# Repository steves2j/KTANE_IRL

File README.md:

# KTANE_IRL
Keep Talking and Nobody Explosed in real Life

#Aid Memory
python3 -m pip install -r ../CanBusSysFirmware/micropython/tools/mpremote/requirements.txt

python3 ../CanBusSysFirmware/micropython/tools/mpremote/mpremote.py connect /dev/cu.usbmodem1411401 fs cp ktane_who_on_first.py :main.py

python3 ../CanBusSysFirmware/micropython/tools/mpremote/mpremote.py connect /dev/cu.usbmodem1411401
exec(open("main.py").read())

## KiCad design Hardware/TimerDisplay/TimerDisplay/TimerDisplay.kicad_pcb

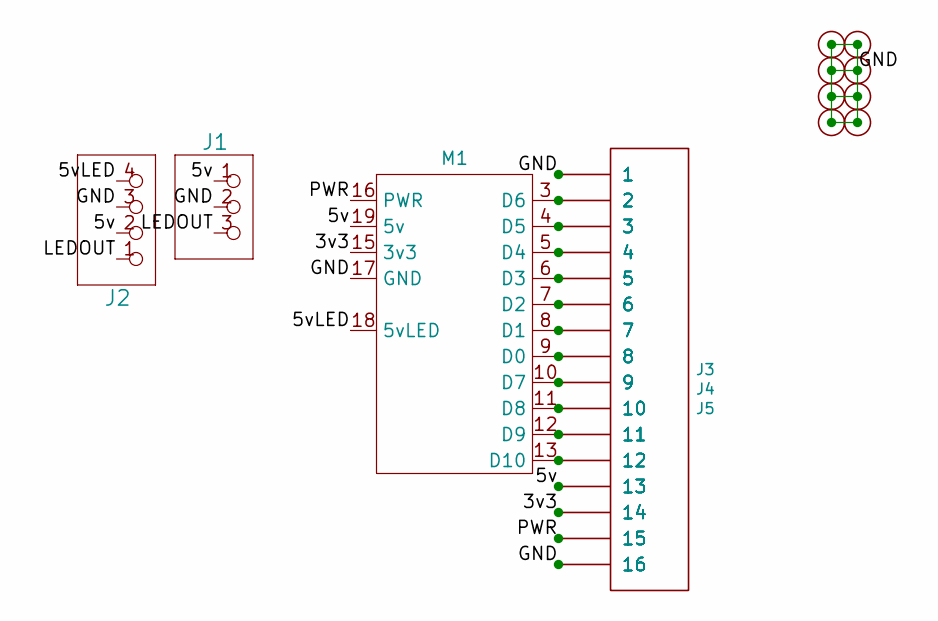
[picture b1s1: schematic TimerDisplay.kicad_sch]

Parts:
H1, H2, H3, H4, H5, H6, H7, H8: Hole; 3mm_pth
J1: HEADER-1X3; 1X03_ROUND
J2: HEADER-1X4; 1X04_LED
J3, J4, J5: HEADER-1X16R; 1X16_ROUND
M1: CanBusModule-BottomCan

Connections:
/3v3: J3.14, J4.14, J5.14, M1.15 (3v3)
/5v: J1.1, J2.2, J3.13, J4.13, J5.13, M1.14 (5v), M1.19 (5v)
/5vLED: J2.4, M1.18 (5vLED)
/GND: H1.1, H2.1, H3.1, H4.1, H5.1, H6.1, H7.1, H8.1, J1.2, J2.3, J3.1, J3.16, J4.1, J4.16, J5.1, J5.16, M1.1 (GND), M1.2 (GND), M1.17 (GND)
/LEDOUT: J1.3, J2.1
/PWR: J3.15, J4.15, J5.15, M1.16 (PWR)
unnamed: J3.8, J4.8, J5.8, M1.9 (D0)
unnamed: J3.7, J4.7, J5.7, M1.8 (D1)
unnamed: J3.6, J4.6, J5.6, M1.7 (D2)
unnamed: J3.5, J4.5, J5.5, M1.6 (D3)
unnamed: J3.4, J4.4, J5.4, M1.5 (D4)
unnamed: J3.3, J4.3, J5.3, M1.4 (D5)
unnamed: J3.2, J4.2, J5.2, M1.3 (D6)
unnamed: J3.9, J4.9, J5.9, M1.10 (D7)
unnamed: J3.10, J4.10, J5.10, M1.11 (D8)
unnamed: J3.11, J4.11, J5.11, M1.12 (D9)
unnamed: J3.12, J4.12, J5.12, M1.13 (D10)

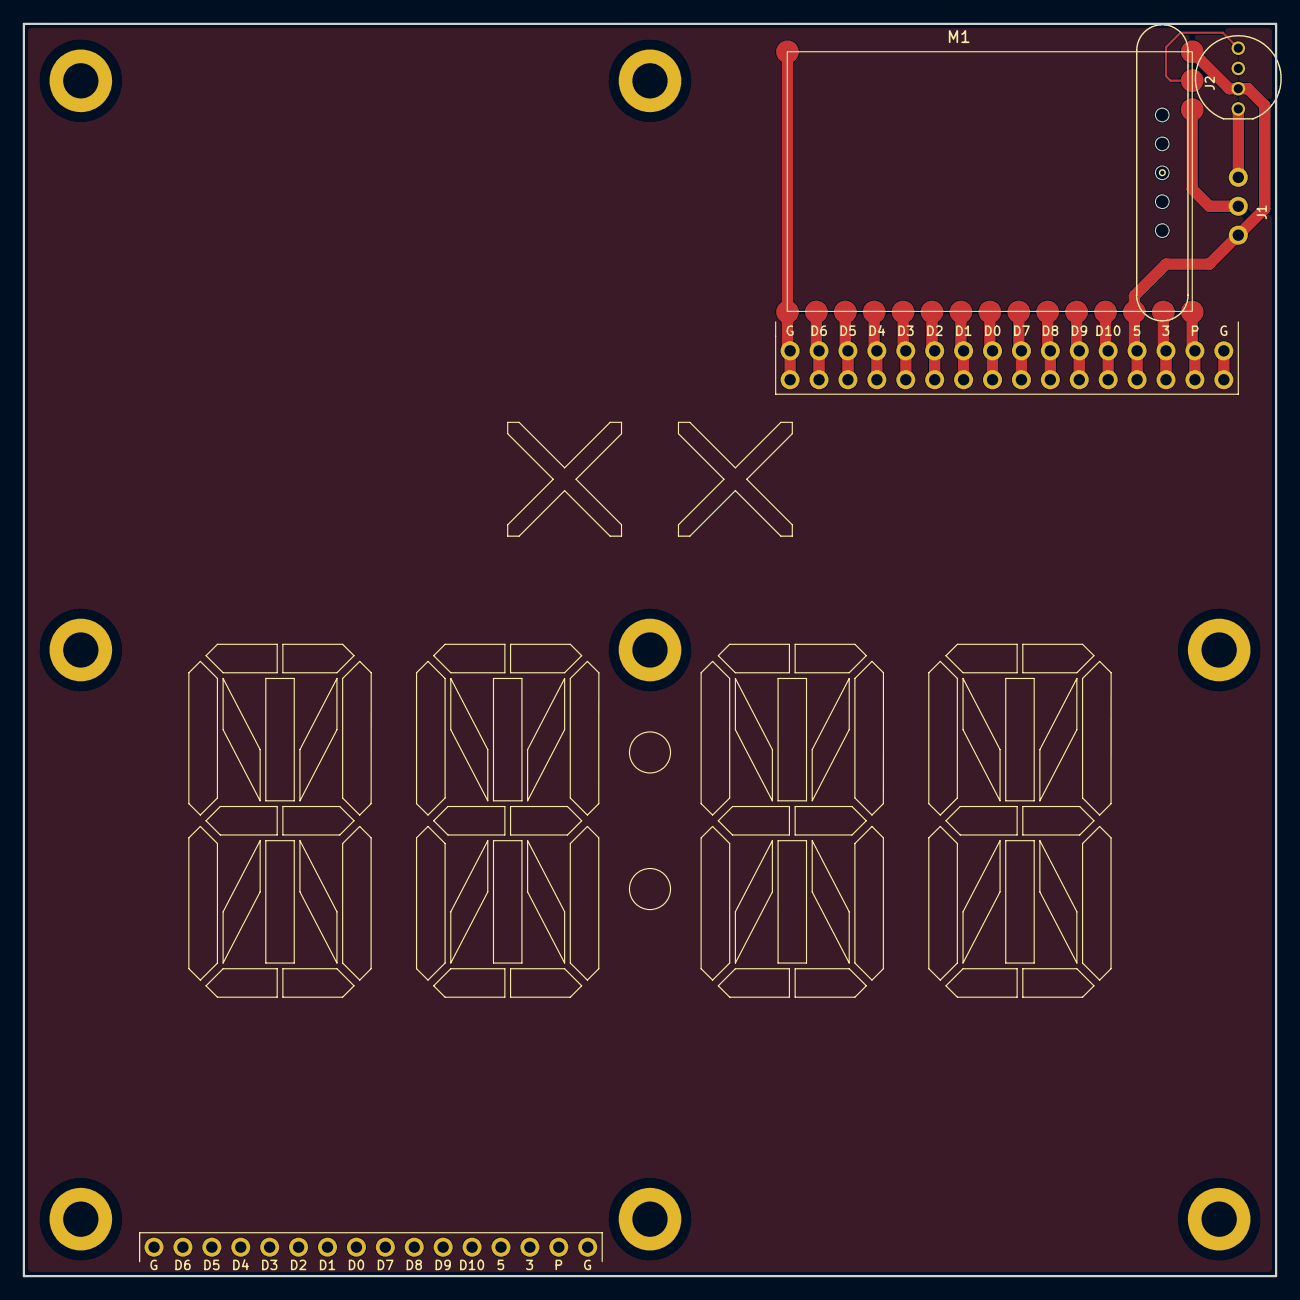
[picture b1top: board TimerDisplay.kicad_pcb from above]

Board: 4 copper layers, 110.0 x 110.0 mm, 14 parts (0 on the bottom side), 17 nets.

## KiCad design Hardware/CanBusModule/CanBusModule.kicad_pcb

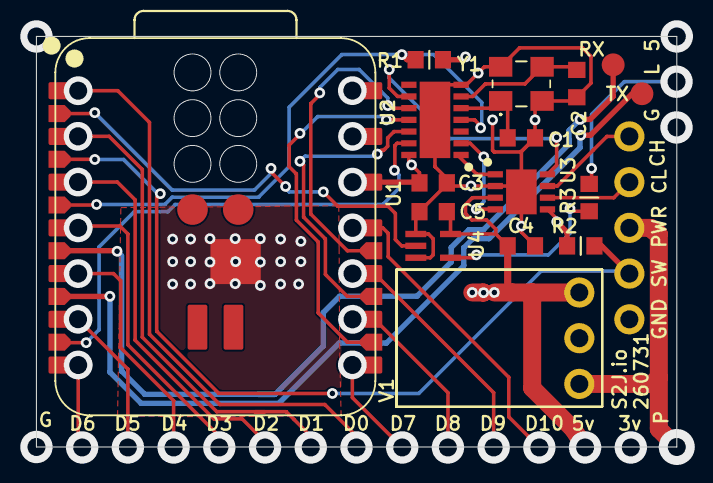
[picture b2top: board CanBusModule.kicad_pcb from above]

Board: 4 copper layers, 35.6 x 22.8 mm, 17 parts (0 on the bottom side), 21 nets.

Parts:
C1, C2: 22pF; _0603MP_CAP3DMODEL
C3, C4, C5: 100nF; _0603MP_CAP3DMODEL
JP1: HEADER-1X5; 1X05_ROUND
R1, R2: 4k7; _0603MP
R3: 330; _0603MP
TP1, TP2: PAD.03X.05
U1: XIAO-ESP32-S3-Plus-SMD
U2: MCP2518FDT-E_QBB; SON65P300X450X90-15N-D
U3: ATA6561-GBQW-N; SON65P300X300X90-9N-D
U4: 74HCT1G125GW; SOT65P210X110-5N
V1: D45V5F5; D45V5F3
Y1: ECS-400-15-33B-CTN-TR; ECS2501033BCKMTR

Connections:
/3v3: C3.2, R1.2, R2.2, U1.12 (3V3_OUT), U2.14 (VDD), U3.5 (VIO)
/5v: C4.1, C5.1, U1.14 (VBUS), U3.3 (VCC), U4.5 (VCC), V1.VOUT
/CANH: JP1.5, U3.7 (CANH)
/CANL: JP1.4, U3.6 (CANL)
/CANMISO: U1.22 (D18), U2.12 (SDO)
/CANMOSI: U1.21 (D19), U2.11 (SDI)
/CANSCK: U1.23 (D17), U2.10 (SCK)
/LED: U1.15 (D11), U4.2 (A)
/OSC1: C2.2, U2.6 (OSC1), Y1.3 (OUT/IN)
/OSC2: C1.1, U2.5 (OSC2), Y1.1 (IN/OUT)
/PWR: JP1.3, V1.VIN
/RX1: TP1.P$1 (1_P$1), U1.18 (D14)
/RXCAN: U2.2 (RXCAN), U3.4 (RXD)
/SW: JP1.2, R2.1, U1.16 (D12)
/TX1: TP2.P$1 (1_P$1), U1.19 (D15)
/TXCAN: U2.1 (TXCAN), U3.1 (TXD)
/~CANCS: U1.20 (D16), U2.13 (NCS)
/~CANINT: R1.1, U1.17 (D13), U2.4 (~INT)
GND: C1.2, C2.1, C3.1, C4.2, C5.2, JP1.1, U1.13 (GND), U2.7 (VSS), U2.15 (EP), U3.2 (GND), U3.9 (EP), U4.1 (~OE), U4.3 (GND), V1.GND, Y1.2 (GND_1), Y1.4 (GND_2)
unnamed: U2.9 (~INT0/GPIO0/XSTBY), U3.8 (STBY)
unnamed: R3.1, U4.4 (Y)

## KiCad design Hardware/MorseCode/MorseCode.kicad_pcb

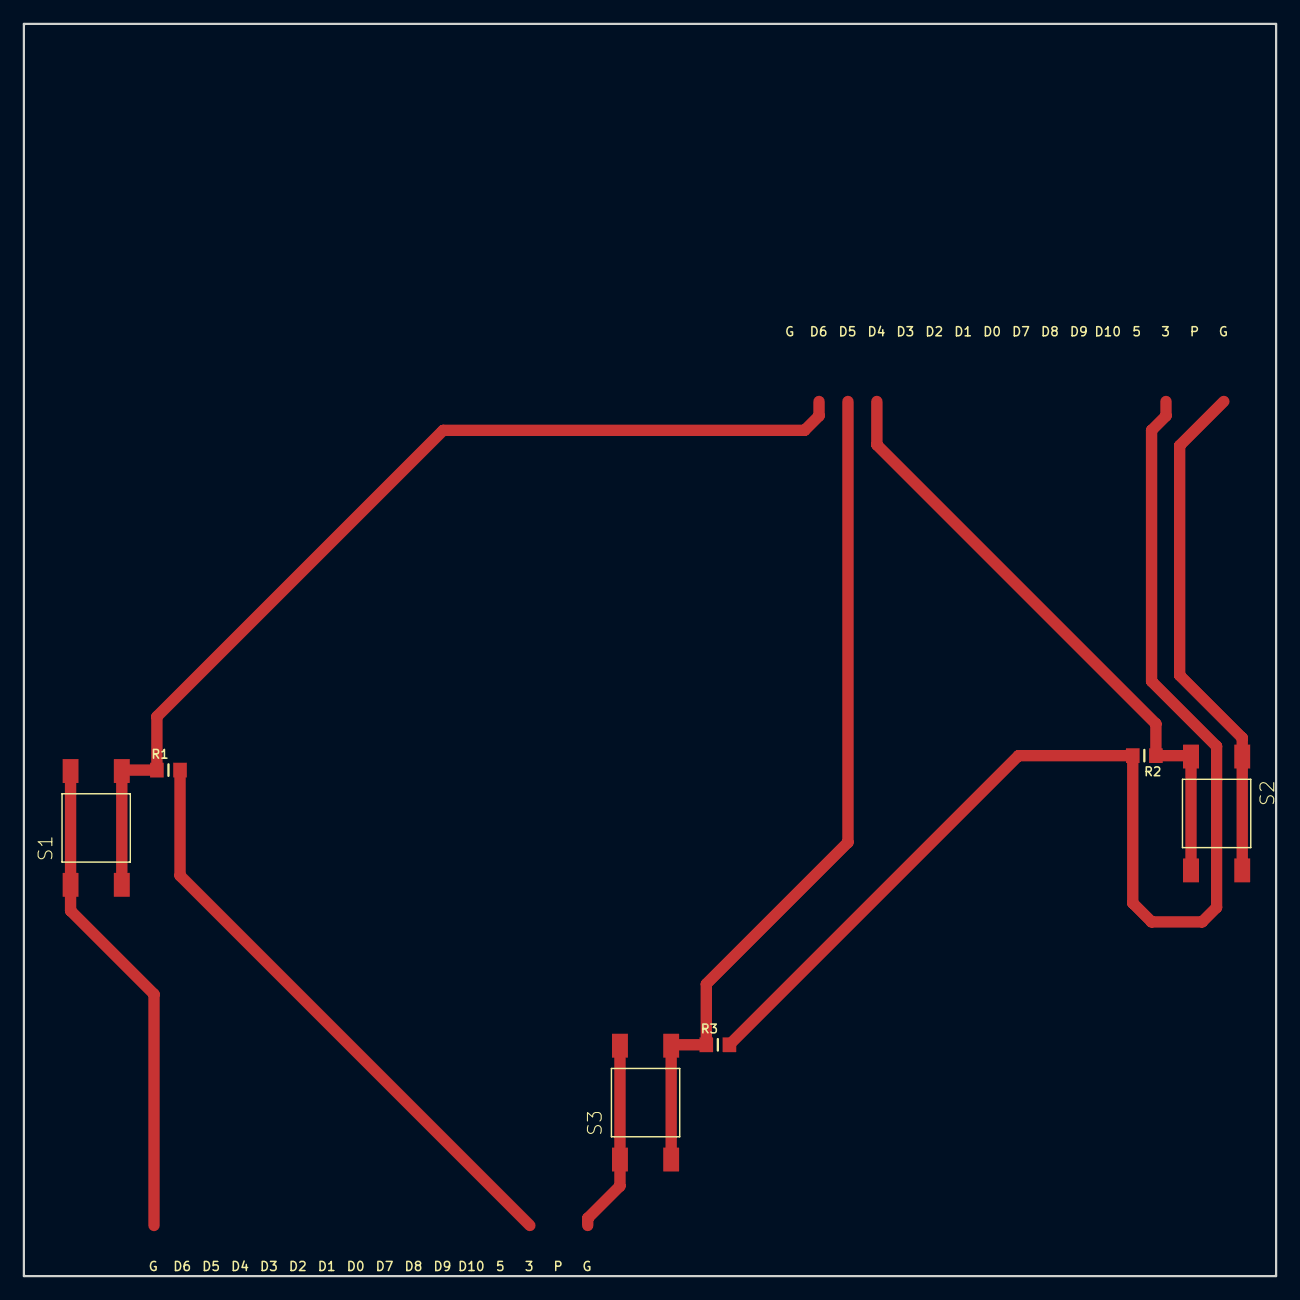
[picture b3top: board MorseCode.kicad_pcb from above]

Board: 2 copper layers, 110.0 x 110.0 mm, 7 parts (0 on the bottom side), 5 nets.

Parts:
R1, R2, R3: 10k; _0805MP
S1: MinusFreq; LSH
S2: PlusFreq; LSH
S3: Transmit; LSH
Z1: KTANEIRLLaserOutline

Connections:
/3v3: R1.2, R2.2, R3.2
/D4: R2.1, S2.3, S2.4
/D5: R3.1, S3.3, S3.4
/D6: R1.1, S1.3, S1.4
GND: S1.1, S1.2, S2.1, S2.2, S3.1, S3.2
